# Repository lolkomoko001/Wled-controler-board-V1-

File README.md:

# Welcome,
<br> 
<br> 
<br> 

## This is Wled software controller board  for addressable led strip  

### Pretty easy to operate: 
You just need to buy all parts from the BOM list  and order the pcb board and connect few wires :)

##  For 5 Volts addressable leds 
find working  5V DC power suplly and conect to screw terminals 

The bottom  terminal are for powering  addressable led strip. 
<br> 
And don't forget to connect signal cable from the signal pad   best to use shielding cable for less noise then use small via to connect one end of shield in the cable 
<br>   

<br> 
<br> 
<br> 

## For 12 to 24 Volts addressable leds strip
You will need 12 to 24V power supply. 
<br>
Now  we will now dont connect the bottom terminal thats only for powering 5V addressable leds. 
<br> 
<br>
But  we will need buck boost or converter  for powering the board  so you will need to buy something like this 
<br>
<br>

<br>
(ilustrative)
<br>
If we want to push their  current from these we will need some type of cooling  like heatsink (like this one up) and maybe small cooling fan. 
<br>

You will conect  it like this.
<br>
IF you have use the shielding cable for better noise resistance.
<br>
#### I have 2 wires in my cable so one is for data (red) and and connect the foil to other  unused  wire only to one end and wire it to small hole near signal pad.  !! 
<br>
I have this https://www.aliexpress.com/item/1005004141251024.html
<br>
# But before connecting the board  check output voltage at the buck converter  with multimeter it should output 5 V if not rotate the rotary encoder till its 5V !!
<br>
<br>
if not it could fry the board don't ask how I know :D 
<br>

<br>

(ilustrative) 

# Finally
Install official software from this website  https://install.wled.me/

---
### Some more photos :))

This is the cost to make the board and assembly  components C2,C4, and U1, 
<br>
I picked  black silkscreen and hasl lead free. everything other is the cheapest

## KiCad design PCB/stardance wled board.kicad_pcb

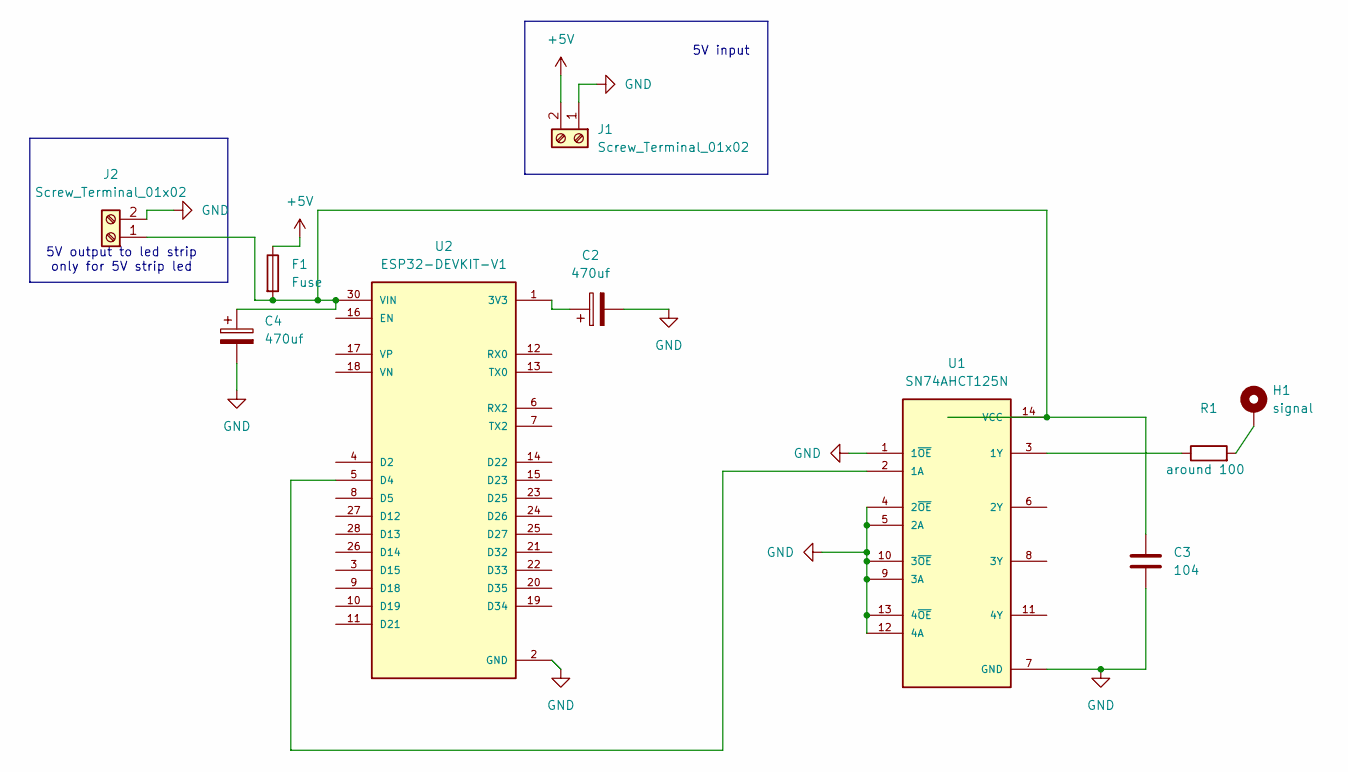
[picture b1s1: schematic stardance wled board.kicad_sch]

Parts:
C2, C4: 470uf; CP_Radial_D10.0mm_P5.00mm
C3: 104; C_Disc_D8.0mm_W5.0mm_P5.00mm
F1: Fuse; Fuseholder_Clip-5x20mm_Schurter_CQM_Inline_P20.60x5.00mm_D1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
H1: signal; MountingHole_2.5mm_Pad
J1, J2: Screw_Terminal_01x02; TerminalBlock_Phoenix_MPT-0,5-2-2.54_1x02_P2.54mm_Horizontal
R1: around 100; R_Axial_DIN0309_L9.0mm_D3.2mm_P12.70mm_Horizontal
U1: SN74AHCT125N; DIP794W45P254L1930H508Q14; PARTREV Q
U2: ESP32-DEVKIT-V1; MODULE_DEVKIT_V1_ESP32-WROOM-32; PARTREV N/A

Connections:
+5V: F1.1, J1.2
GND: C2.2, C3.2, C4.2, J1.1, J2.2, U1.1 (1~OE), U1.4 (2~OE), U1.5 (2A), U1.7 (GND), U1.9 (3A), U1.10 (3~OE), U1.12 (4A), U1.13 (4~OE), U2.2 (GND), U2.29 (GND)
unnamed: H1.1 (1_1), R1.2
unnamed: C3.1, C4.1, F1.2, J2.1, U1.14 (VCC), U2.30 (VIN)
unnamed: U1.2 (1A), U2.5 (D4)
unnamed: R1.1, U1.3 (1Y)
unnamed: C2.1, U2.1 (3V3)

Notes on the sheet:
5V input
5V output to led strip only for 5V strip led

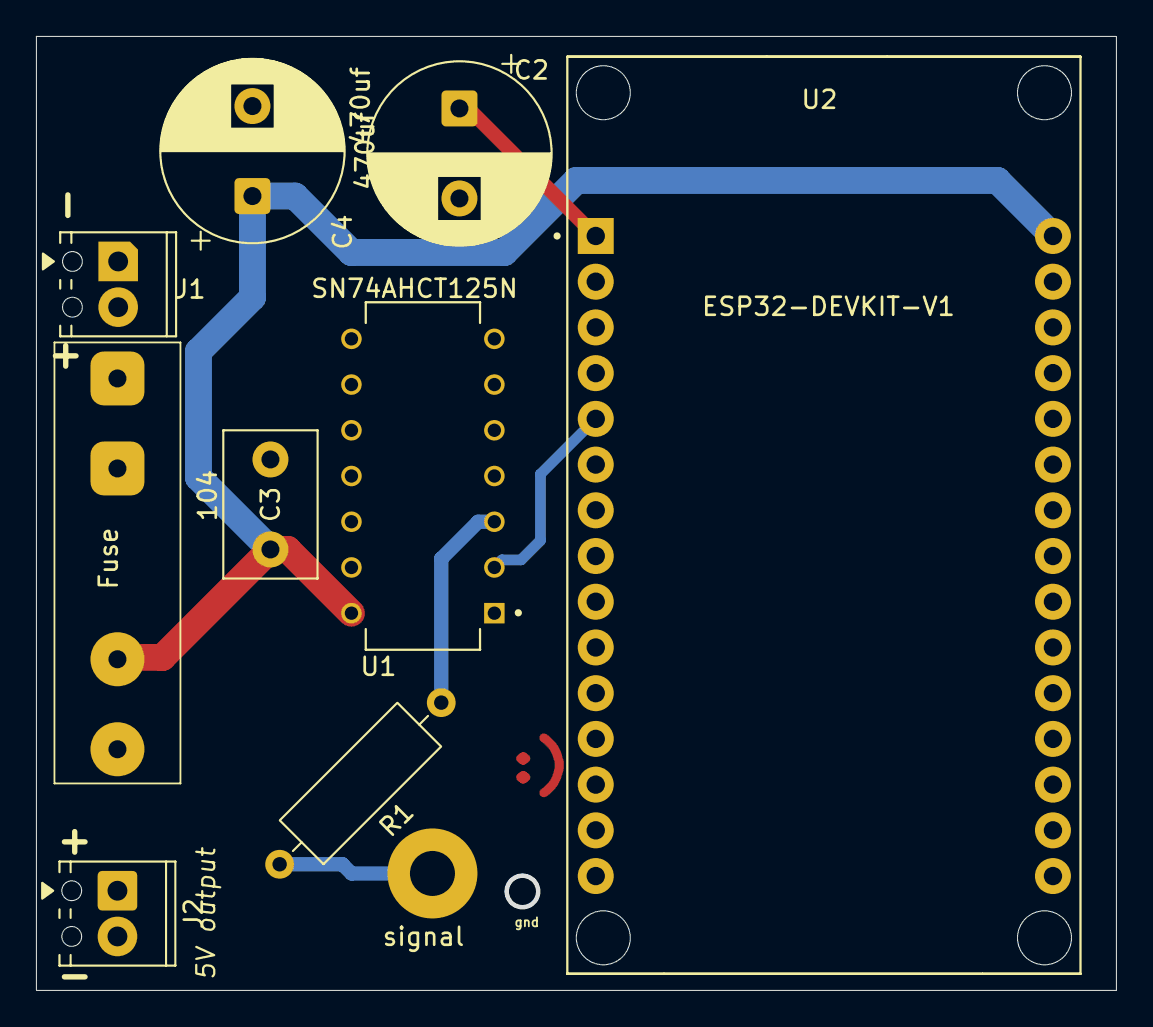
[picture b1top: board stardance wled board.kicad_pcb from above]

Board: 2 copper layers, 60.0 x 53.0 mm, 10 parts (1 on the bottom side), 7 nets.
